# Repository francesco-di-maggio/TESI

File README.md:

# TESI — TANGIBLE AND EMBODIED SOUND INTERACTION

## About
TESI (Tangible and Embodied Sound Interaction) is a modular toolkit for exploring sound in distributed systems of tangible interfaces. It links gestures, materials and spatial relationships to sound.

TESI has three layers:
* **Node**: hardware that senses and, from V3, makes sound.
* **Network**: how nodes and computers communicate (OSC, OOCSI, ESP-NOW).
* **Mapping**: from sensor data to sound, in Max on a computer or Pure Data on the node.

Documentation: **[francescodimaggio.nl/tesi](https://francescodimaggio.nl/tesi/)**

## Versions
| Version | Board | Sound | Files |
|---|---|---|---|
| V3 | Waveshare ESP32-S3-AUDIO-Board | On the node (Pure Data) | In progress, see the site |
| V2 | Custom PCB, Adafruit ESP32 Feather V2 | On a computer (Max) | `arduino/`, `kicad/`, `max/`, `oocsi/`, `ableton/` |
| V1 | Breadboard, Adafruit ESP32 Feather | On a computer (Max) | — |

## Repository Contents
* `arduino/` – V2 firmware for sensor data collection and communication.
* `kicad/` – V2 schematics and PCB layout.
* `max/` – Max patches for data processing, mapping and control.
* `oocsi/` – OOCSI local server.
* `ableton/` – Example Ableton Live set.
* `events/` – Material from workshops and conferences.
* `site/` – Source of the documentation site (Astro).

## Get Started
Setup for V2 (firmware, libraries, OOCSI, Max) is on the [V2 page](https://francescodimaggio.nl/tesi/versions/v2/). Firmware details are in [`arduino/README.md`](arduino/README.md).

## Publications
* Francesco Di Maggio, Bart Hengeveld, Mathias Funk, and Rebecca Fiebrink. 2026. TESI: A Toolkit for Tangible and Embodied Sound Interaction. In *TEI '26*. ACM. https://doi.org/10.1145/3731459.3779334
* Francesco Di Maggio, Bart Hengeveld, and Mathias Funk. 2025. [Making Sense of Decentralized TUIs: A Modular Sound-Centric Approach](https://dl.acm.org/doi/10.1145/3689050.3708332). In *TEI '25*. ACM. https://doi.org/10.1145/3689050.3708332

## Contribute & Collaborate
TESI is open-source, and contributions are welcome:

* Expanding hardware (sensor integration, PCB improvements)
* Enhancing software (Max patches, mappings, sound engines)
* Exploring new applications (live performance, installations, research)

Fork this repository, submit pull requests, or start a discussion in the issues section.

## Credits
### PCB Layout & Schematics
Designed and assembled at TU/e in the [d.search lab](https://research.tue.nl/en/equipments/dsearch-lab) with [Katrien van Riet](https://www.vectorious.nl/) and Geert van den Boomen.

### OOCSI to Plugdata/Max Implementation
Designed at TU/e with [Mathias Funk](https://mathias-funk.com/).

## License
MIT. See [LICENSE](LICENSE) for details.

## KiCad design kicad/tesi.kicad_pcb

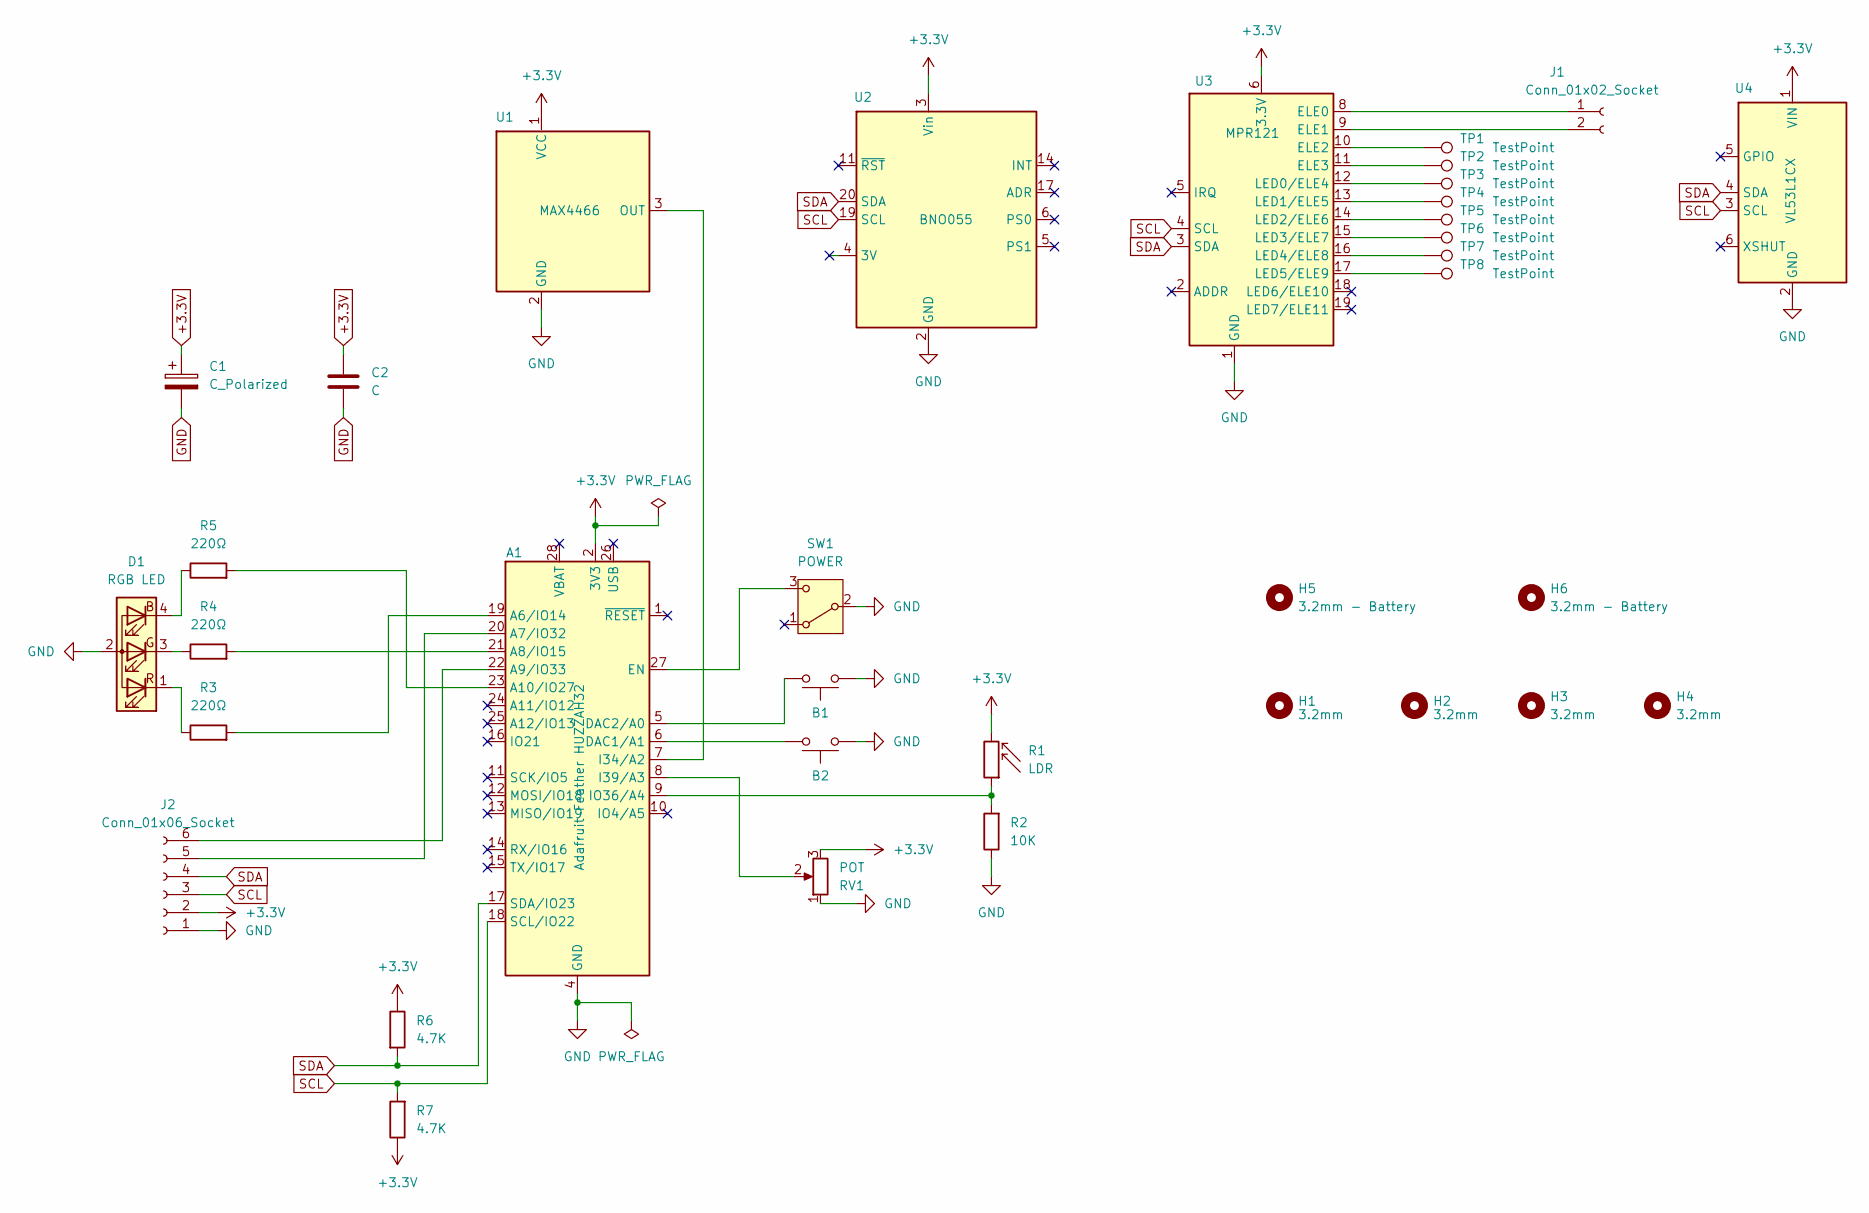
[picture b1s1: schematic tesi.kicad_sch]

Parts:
A1: Adafruit Feather HUZZAH32; Adafruit ESP32 Feather
B1, B2: SW_PUSH_6mm
C1: C_Polarized; CP_Radial_D4.0mm_P2.00mm
C2: C; C_Disc_D4.3mm_W1.9mm_P5.00mm
D1: RGB LED; LED_D5.0mm-4_RGB_Wide_Pins
H1, H2, H3, H4: 3.2mm; MountingHole_3.2mm_M3
H5, H6: 3.2mm - Battery; MountingHole_3.2mm_M3
J1: Conn_01x02_Socket; PinSocket_1x02_P2.54mm_Vertical
J2: Conn_01x06_Socket; PinSocket_1x06_P2.54mm_Vertical
R1: LDR; R_LDR_4.9x4.2mm_P2.54mm_Vertical
R2: 10K; R_Axial_DIN0207_L6.3mm_D2.5mm_P10.16mm_Horizontal
R3, R4, R5: 220Ω; R_Axial_DIN0207_L6.3mm_D2.5mm_P10.16mm_Horizontal
R6, R7: 4.7K; R_Axial_DIN0207_L6.3mm_D2.5mm_P10.16mm_Horizontal
RV1: POT; Potentiometer_TT_P0915N
SW1: POWER; Switch
TP1, TP2, TP3, TP4, TP5, TP6, TP7, TP8: TestPoint; TouchPad - 4.0mm
U1: MAX4466
U2: BNO055
U3: MPR121
U4: VL53L1CX; VL53L1X

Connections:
+3.3V: A1.2 (3V3), C1.1, C2.1, J2.2, R1.2, R6.1, R7.1, RV1.3, U1.1 (VCC), U2.3 (Vin), U3.6 (3.3V), U4.1 (VIN)
GND: A1.4 (GND), B1.1, B2.1, C1.2, C2.2, D1.2 (A), J2.1, R2.1, RV1.1, SW1.2 (B), U1.2 (GND), U2.2 (GND), U3.1 (GND), U4.2 (GND)
unnamed: A1.19 (A6/IO14), R3.2
unnamed: A1.20 (A7/IO32), J2.5
unnamed: A1.21 (A8/IO15), R4.2
unnamed: A1.22 (A9/IO33), J2.6
unnamed: A1.23 (A10/IO27), R5.2
unnamed: A1.6 (DAC1/A1), B2.2
unnamed: A1.5 (DAC2/A0), B1.2
unnamed: A1.27 (EN), SW1.3 (C)
unnamed: A1.7 (I34/A2), U1.3 (OUT)
unnamed: A1.8 (I39/A3), RV1.2
unnamed: A1.9 (IO36/A4), R1.1, R2.2
unnamed: D1.4 (BK), R5.1
unnamed: D1.3 (GK), R4.1
unnamed: D1.1 (RK), R3.1
unnamed: J1.1, U3.8 (ELE0)
unnamed: J1.2, U3.9 (ELE1)
unnamed: TP1.1, U3.10 (ELE2)
unnamed: TP2.1, U3.11 (ELE3)
unnamed: TP3.1, U3.12 (LED0/ELE4)
unnamed: TP4.1, U3.13 (LED1/ELE5)
unnamed: TP5.1, U3.14 (LED2/ELE6)
unnamed: TP6.1, U3.15 (LED3/ELE7)
unnamed: TP7.1, U3.16 (LED4/ELE8)
unnamed: TP8.1, U3.17 (LED5/ELE9)
SCL: A1.18 (SCL/IO22), J2.3, R7.2, U2.19 (SCL), U3.4 (SCL), U4.3 (SCL)
SDA: A1.17 (SDA/IO23), J2.4, R6.2, U2.20 (SDA), U3.3 (SDA), U4.4 (SDA)

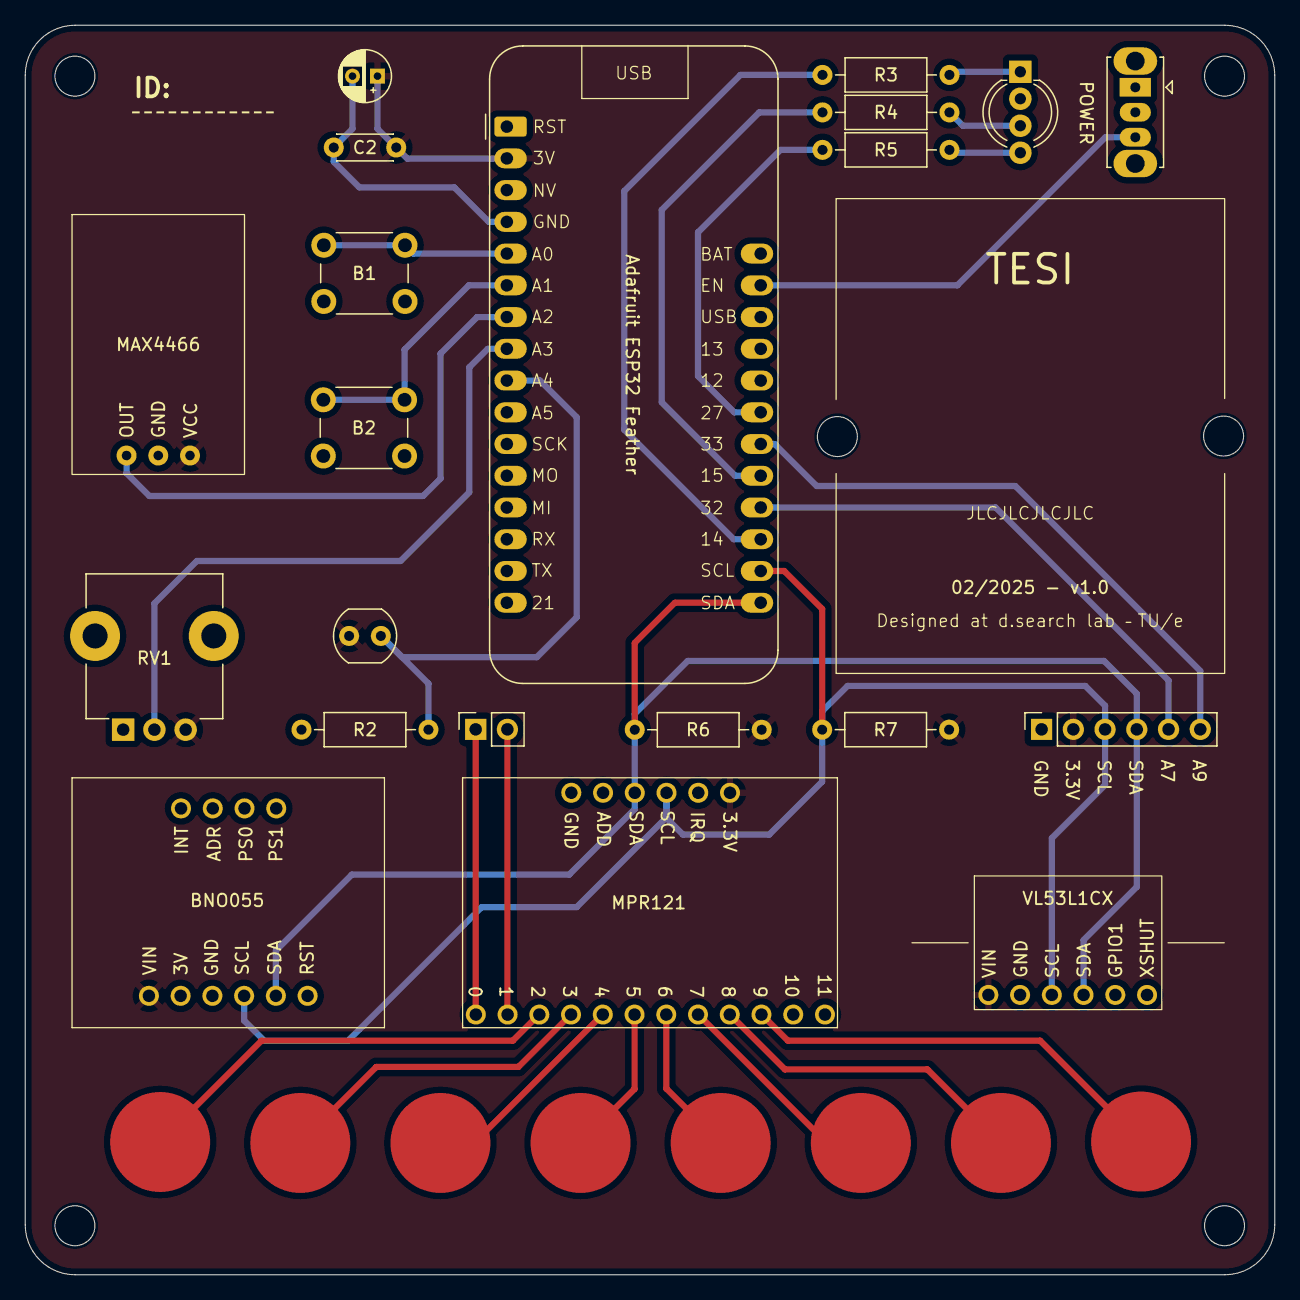
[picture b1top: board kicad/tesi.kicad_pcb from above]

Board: 2 copper layers, 100.0 x 100.0 mm, 35 parts (0 on the bottom side), 28 nets.

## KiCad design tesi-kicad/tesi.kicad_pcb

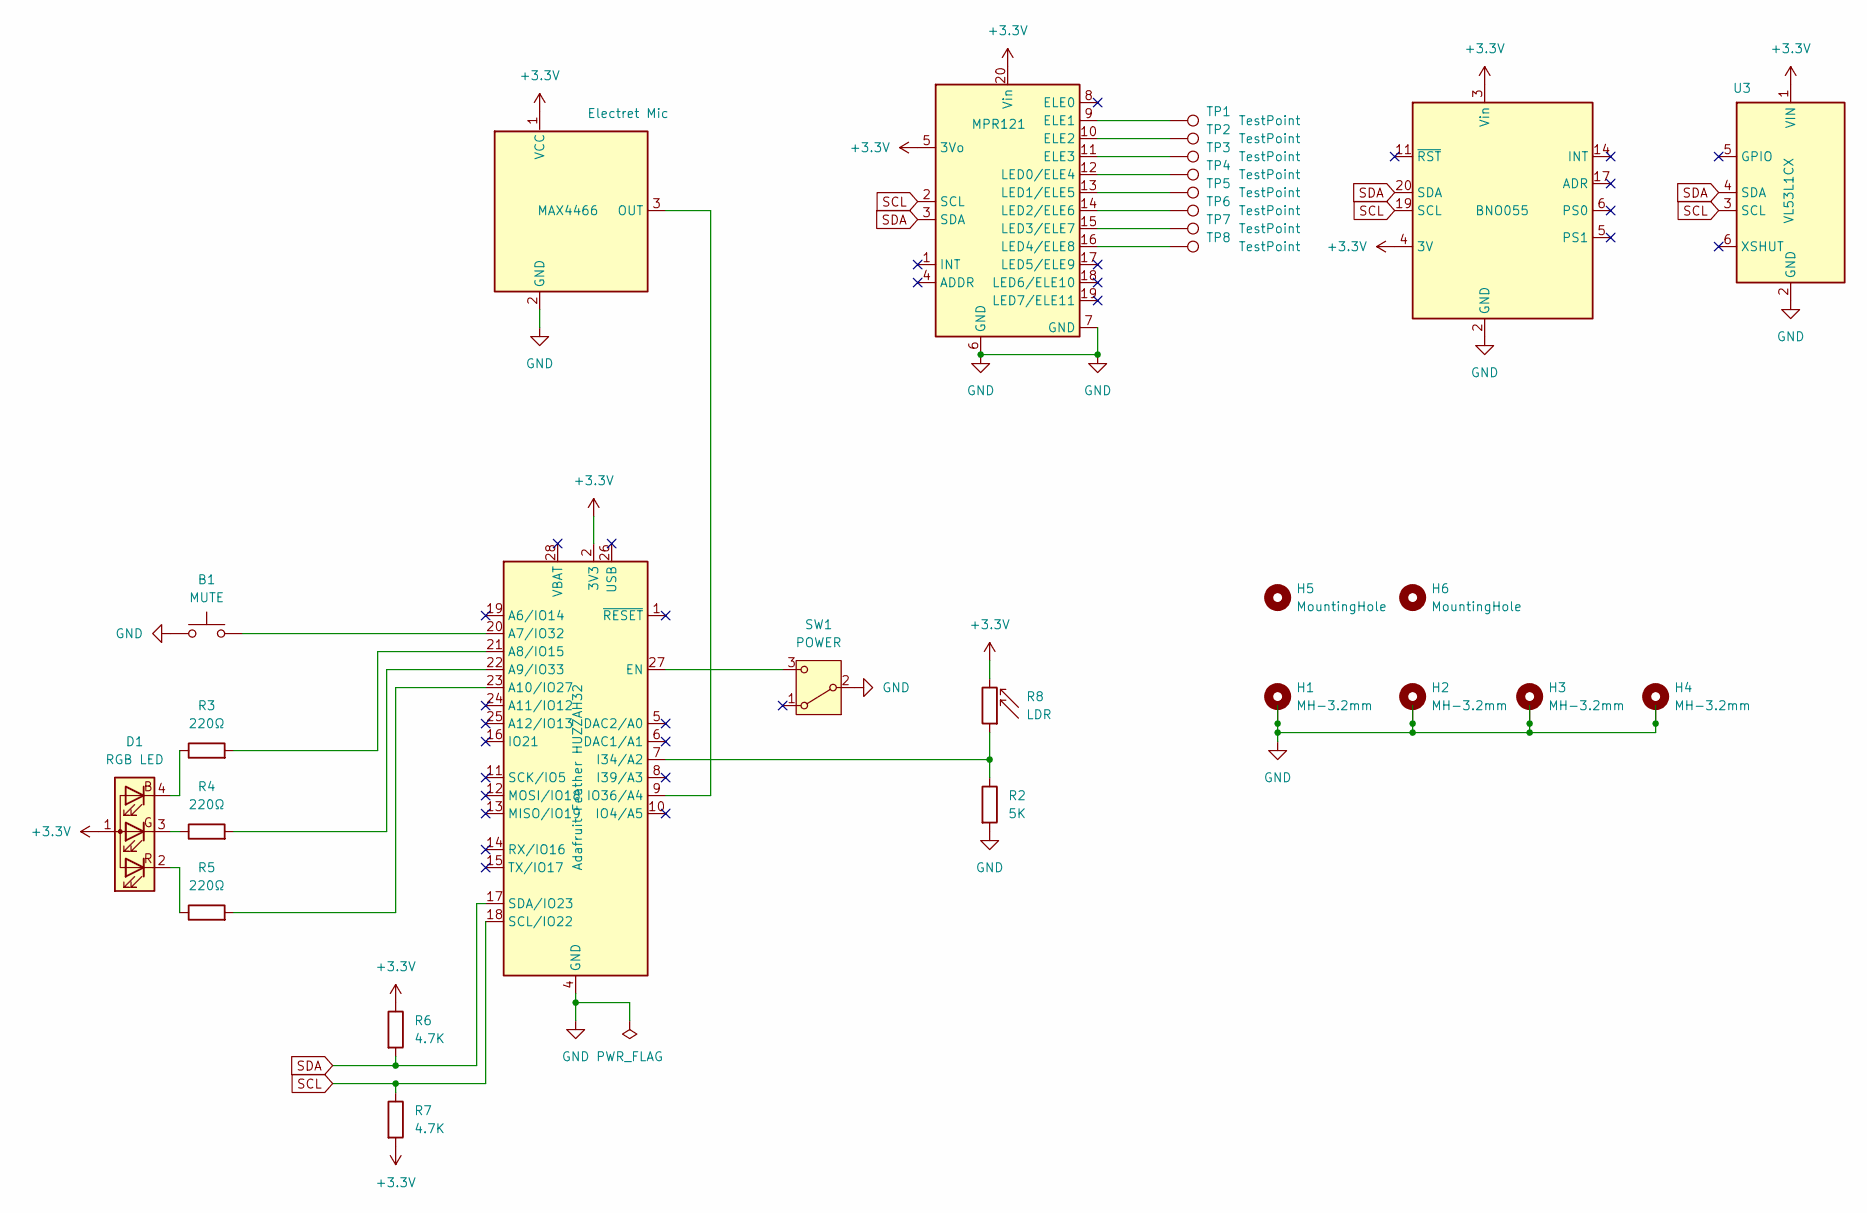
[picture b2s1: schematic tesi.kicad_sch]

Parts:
A2: Adafruit Feather HUZZAH32; Adafruit HUZZAH32 Feather Board - WithoutMountingHoles
B1: MUTE; SW_PUSH_6mm
D1: RGB LED; LED_D5.0mm-4_RGB_Wide_Pins
H1, H2, H3, H4: MH-3.2mm; MountingHole_3.2mm_M3
H5, H6: MountingHole; MountingHole_4mm
MAX4466: Electret Mic; MAX4466
R2: 5K; R_Axial_DIN0207_L6.3mm_D2.5mm_P7.62mm_Horizontal
R3, R4, R5: 220Ω; R_Axial_DIN0207_L6.3mm_D2.5mm_P7.62mm_Horizontal
R6, R7: 4.7K; R_Axial_DIN0207_L6.3mm_D2.5mm_P7.62mm_Horizontal
R8: LDR; R_LDR_4.9x4.2mm_P2.54mm_Vertical
SW1: POWER; SW_Slide_SPDT_Angled_CK_OS102011MA1Q
TP1, TP2, TP3, TP4, TP5, TP6, TP7, TP8: TestPoint; TestPoint_Pad_D4.0mm
U2: BNO055
U3: VL53L1CX; VL53L1X
U121: MPR121

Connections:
+3.3V: A2.2 (3V3), D1.1 (A), MAX4466.1 (VCC), R6.1, R7.2, R8.2, U2.3 (Vin), U2.4 (3V), U3.1 (VIN), U121.5 (3Vo), U121.20 (Vin)
GND: A2.4 (GND), B1.1, H1.1, H2.1, H3.1, H4.1, MAX4466.2 (GND), R2.2, SW1.2 (B), U2.2 (GND), U3.2 (GND), U121.6 (GND), U121.7 (GND)
unnamed: A2.20 (A7/IO32), B1.2
unnamed: A2.21 (A8/IO15), R3.2
unnamed: A2.22 (A9/IO33), R4.2
unnamed: A2.23 (A10/IO27), R5.2
unnamed: A2.27 (EN), SW1.3 (C)
unnamed: A2.7 (I34/A2), R2.1, R8.1
unnamed: A2.9 (IO36/A4), MAX4466.3 (OUT)
unnamed: D1.4 (BK), R3.1
unnamed: D1.3 (GK), R4.1
unnamed: D1.2 (RK), R5.1
unnamed: TP1.1, U121.9 (ELE1)
unnamed: TP2.1, U121.10 (ELE2)
unnamed: TP3.1, U121.11 (ELE3)
unnamed: TP4.1, U121.12 (LED0/ELE4)
unnamed: TP5.1, U121.13 (LED1/ELE5)
unnamed: TP6.1, U121.14 (LED2/ELE6)
unnamed: TP7.1, U121.15 (LED3/ELE7)
unnamed: TP8.1, U121.16 (LED4/ELE8)
SCL: A2.18 (SCL/IO22), R7.1, U2.19 (SCL), U3.3 (SCL), U121.2 (SCL)
SDA: A2.17 (SDA/IO23), R6.2, U2.20 (SDA), U3.4 (SDA), U121.3 (SDA)

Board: 2 copper layers, 30 parts (0 on the bottom side), 22 nets, no tracks yet.

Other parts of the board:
LiPo Battery: Battery; Lipo Battery 400 mAh

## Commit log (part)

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2025-02-06 add README.md and .gitignore
2025-02-06 add KiCad files
2025-02-06 add LICENSE
2025-02-07 add files
2025-02-07 add files
2025-02-11 update pcb
2025-02-19 add - to live folder
2025-02-19 removed live folder for debug
2025-02-19 edit gitignore
2025-02-26 add images
2025-09-20 Implement hybrid OSC addressing system with memory optimizations
    - Add three OSC addressing methods: explicit (/INDEX/), generic (/tesi/), and broadcast (/all/)
    - Optimize memory usage with single buffer for address parsing
    - Implement configurable IN_PORT (9001) and OUT_PORT (8001) via secrets.h
    - Add unified DEBUG flag system for consistent debug control
    - Update documentation with simplified startup messages
    - Add complete /all functionality including IP configuration
2025-09-20 Improve boot sequence with clean, professional serial monitor messages
    - Add structured boot sequence with numbered steps (1. WiFi, 2. OSC, 3. Sensors)
    - Clean header with project title and device index
    - WiFi section shows target IP/port where messages are sent
    - OSC section shows local IP/port where device listens
    - Individual sensor status messages (MPR121, VL53L1X, BNO055 > OK)
    - Professional formatting with proper spacing and visual hierarchy
2025-09-21 Optimize sensor timing and OSC performance for musical applications
    - Improve sensor sampling rates for musical timing:
    * PUSH/CAP sensors: 10ms → 5ms (200Hz for musical responsiveness)
    * POT sensor: 20ms → 10ms (100Hz for smooth control)
    * MIC sensor: 40ms → 30ms (33Hz optimized)
    * BATTERY sensor: 4s → 5s (reduced polling frequency)
    - Optimize OSC message handling for performance:
2025-10-27 update for submission
